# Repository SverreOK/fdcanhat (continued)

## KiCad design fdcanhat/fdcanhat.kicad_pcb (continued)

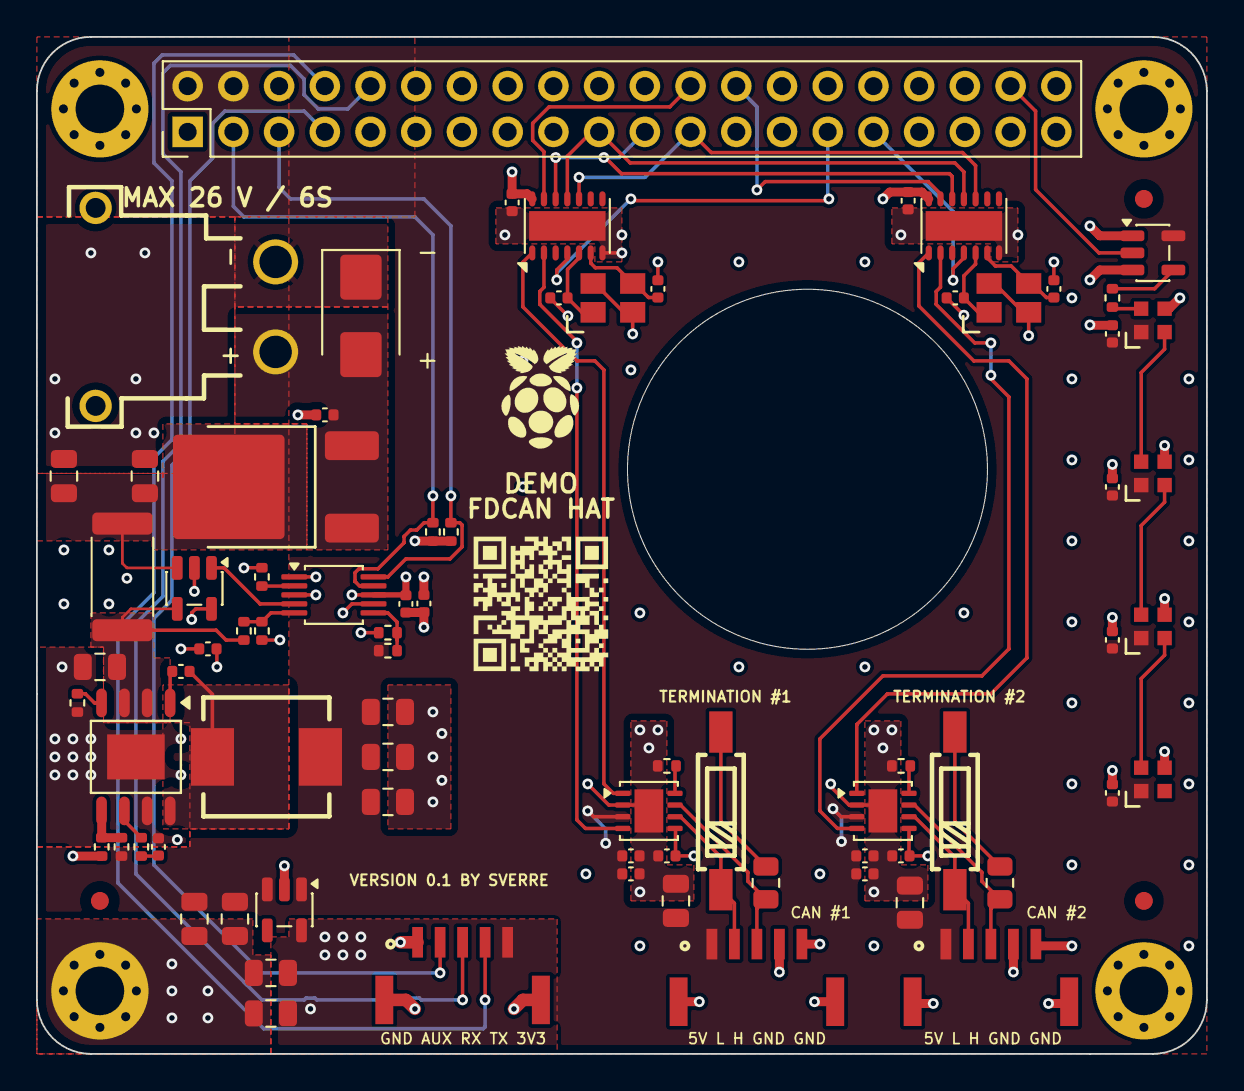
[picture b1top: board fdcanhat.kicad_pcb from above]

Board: 4 copper layers, 65.0 x 56.5 mm, 83 parts (0 on the bottom side), 50 nets.

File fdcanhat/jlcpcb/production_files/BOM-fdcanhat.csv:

Comment,Designator,Footprint,LCSC,Quantity
100k,R2,R_0402_1005Metric,C25741,1
100n 50V X7R,"C1,C18,C19,C21,C25,C26,C28,C31,C32,C33,C34,C36,C4,C6",C_0402_1005Metric,C307331,14
10k,"R11,R13,R15,R16,R17,R3,R6,R9",R_0402_1005Metric,C25744,8
10m,R1,R_2512_6332Metric,C108943,1
10u 50V X5R,"C13,C14,C15,C16,C2,C20,C27,C3,C7",C_0805_2012Metric,C440198,9
120R,"R10,R12",R_0805_2012Metric,C17437,2
15k8,R8,R_0402_1005Metric,C26956,1
1u 25V X7R,"C17,C24,C35",C_0402_1005Metric,C52923,3
20 MHz,"Y1,Y2",CRYSTAL-SMD_4P-L3.2-W2.5-BL-2,C9004,2
200K,R7,R_0402_1005Metric,C25764,1
22R,R14,R_0402_1005Metric,C25092,1
22u 25V X5R,"C10,C11,C9",C_0805_2012Metric,C45783,3
27p 50V C0G,"C22,C23,C29,C30",C_0402_1005Metric,C3889037,4
2n7 50V X7R,C12,C_0402_1005Metric,C106251,1
3.3 uH @ 8.5A,L1,IND-SMD_L7.0-W6.6,C167219,1
33k,R4,R_0402_1005Metric,C25779,1
53k6,R5,R_0402_1005Metric,C53398,1
74AHCT1G125,U8,SOT-23-5,C20617903,1
ADS1115IDGSR,U9,VSSOP-10_3x3mm_P0.5mm,C37593,1
AP64500,U2,SO-8-EP,C2070920,1
GH1.25-5P,"J2,J4,J5",SM05B-GHS-TB-LF-SN,C189896,3
INA180,U1,SOT-23-5,C122228,1
MBR1060CS,D1,TO-252-2_L6.6-W6.1-P4.57-LS10.2-TR-CW,C5220847,1
MCP2518FDT,"U5,U7",DFN-14-1EP_3x4.5mm_P0.65mm_EP1.65x4.25mm,C621395,2
SK6812,"D3,D4,D5,D6",LED-SMD_4P-L2.0-W2.0-BR,C2909058,4
SMBJ28CA,D2,D_SMB,C19077583,1
SPX3819,U3,SOT-23-5,C9055,1
SW_SPST,"SW1,SW2",SW-SMD_DSIC01LSGET,C54948,2
TJA1051TK-3,"U4,U6",HVSON-8-1EP_3x3mm_P0.65mm_EP1.6x2.4mm,C2875699,2

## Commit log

2026-01-08 ish done with schematics
2026-01-09 board layout done, ready for routing
2026-01-15 almost done
2026-01-16 done doublechecking, going for review
2026-01-19 ready for last scrut
2026-01-27 sent to production
